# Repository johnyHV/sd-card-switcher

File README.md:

# SD Card Switcher

A simple hardware device for switching a microSD card between a PC and another SD-card host device. 

<div align="center">

</div>

## Use Cases

Useful for devices where an SD card needs to be frequently accessed from both the target device and a PC, for example:

- Firmware development and testing
- Embedded Linux development
- 3D printers
- Single-board computers
- SD-card based embedded devices
- Easy access to logs and configuration files

The switch changes the physical connection of the SD card; it does not copy or synchronize data.

## How it works

The device contains:

* USB interface for connecting the card to a PC
* microSD card slot
* SD-card-shaped PCB with an SD edge connector
* Hardware switch for selecting the active connection

Insert a microSD card into the onboard slot and plug the SD-shaped PCB into the target device.

The switch selects whether the microSD card is connected to:

* **PC** via USB
* **Target device** via the SD card interface

This allows the same SD card to be easily switched between a computer and the target device without physically removing the card.

## Main Components

| Component              | Part                     |
| ---------------------- | ------------------------ |
| USB/SD card controller | GL827                    |
| Bus switch             | SN74CBT3257D             |
| SD card socket         | 693072010801             |
| USB-C connector        | Molex 105450-0101        |
| Micro USB connector    | Molex 54819-0519         |
| Switch                 | SPDT switch              |
| LED                    | LED                      |
| Passives               | Resistors and capacitors |

## Schematic

## PCB

**PCB thickness: 0.8 mm**

The SD-shaped PCB edge connector requires a 0.8 mm PCB thickness to fit properly into a standard SD card slot.

The PCB was manufactured by [JLCPCB](https://jlcpcb.com/?from=GRVYI). This is a referral link. 

## Files

This repository contains the PCB design files and manufacturing files required to build the SD Card Switcher.

## Disclaimer

This project is provided "as is", without any warranty.

The author is not responsible for any damage to SD cards, connected devices, computers, or other hardware resulting from the use, modification, or construction of this project.

Build and use it at your own risk.

## License

Open-source hardware project.

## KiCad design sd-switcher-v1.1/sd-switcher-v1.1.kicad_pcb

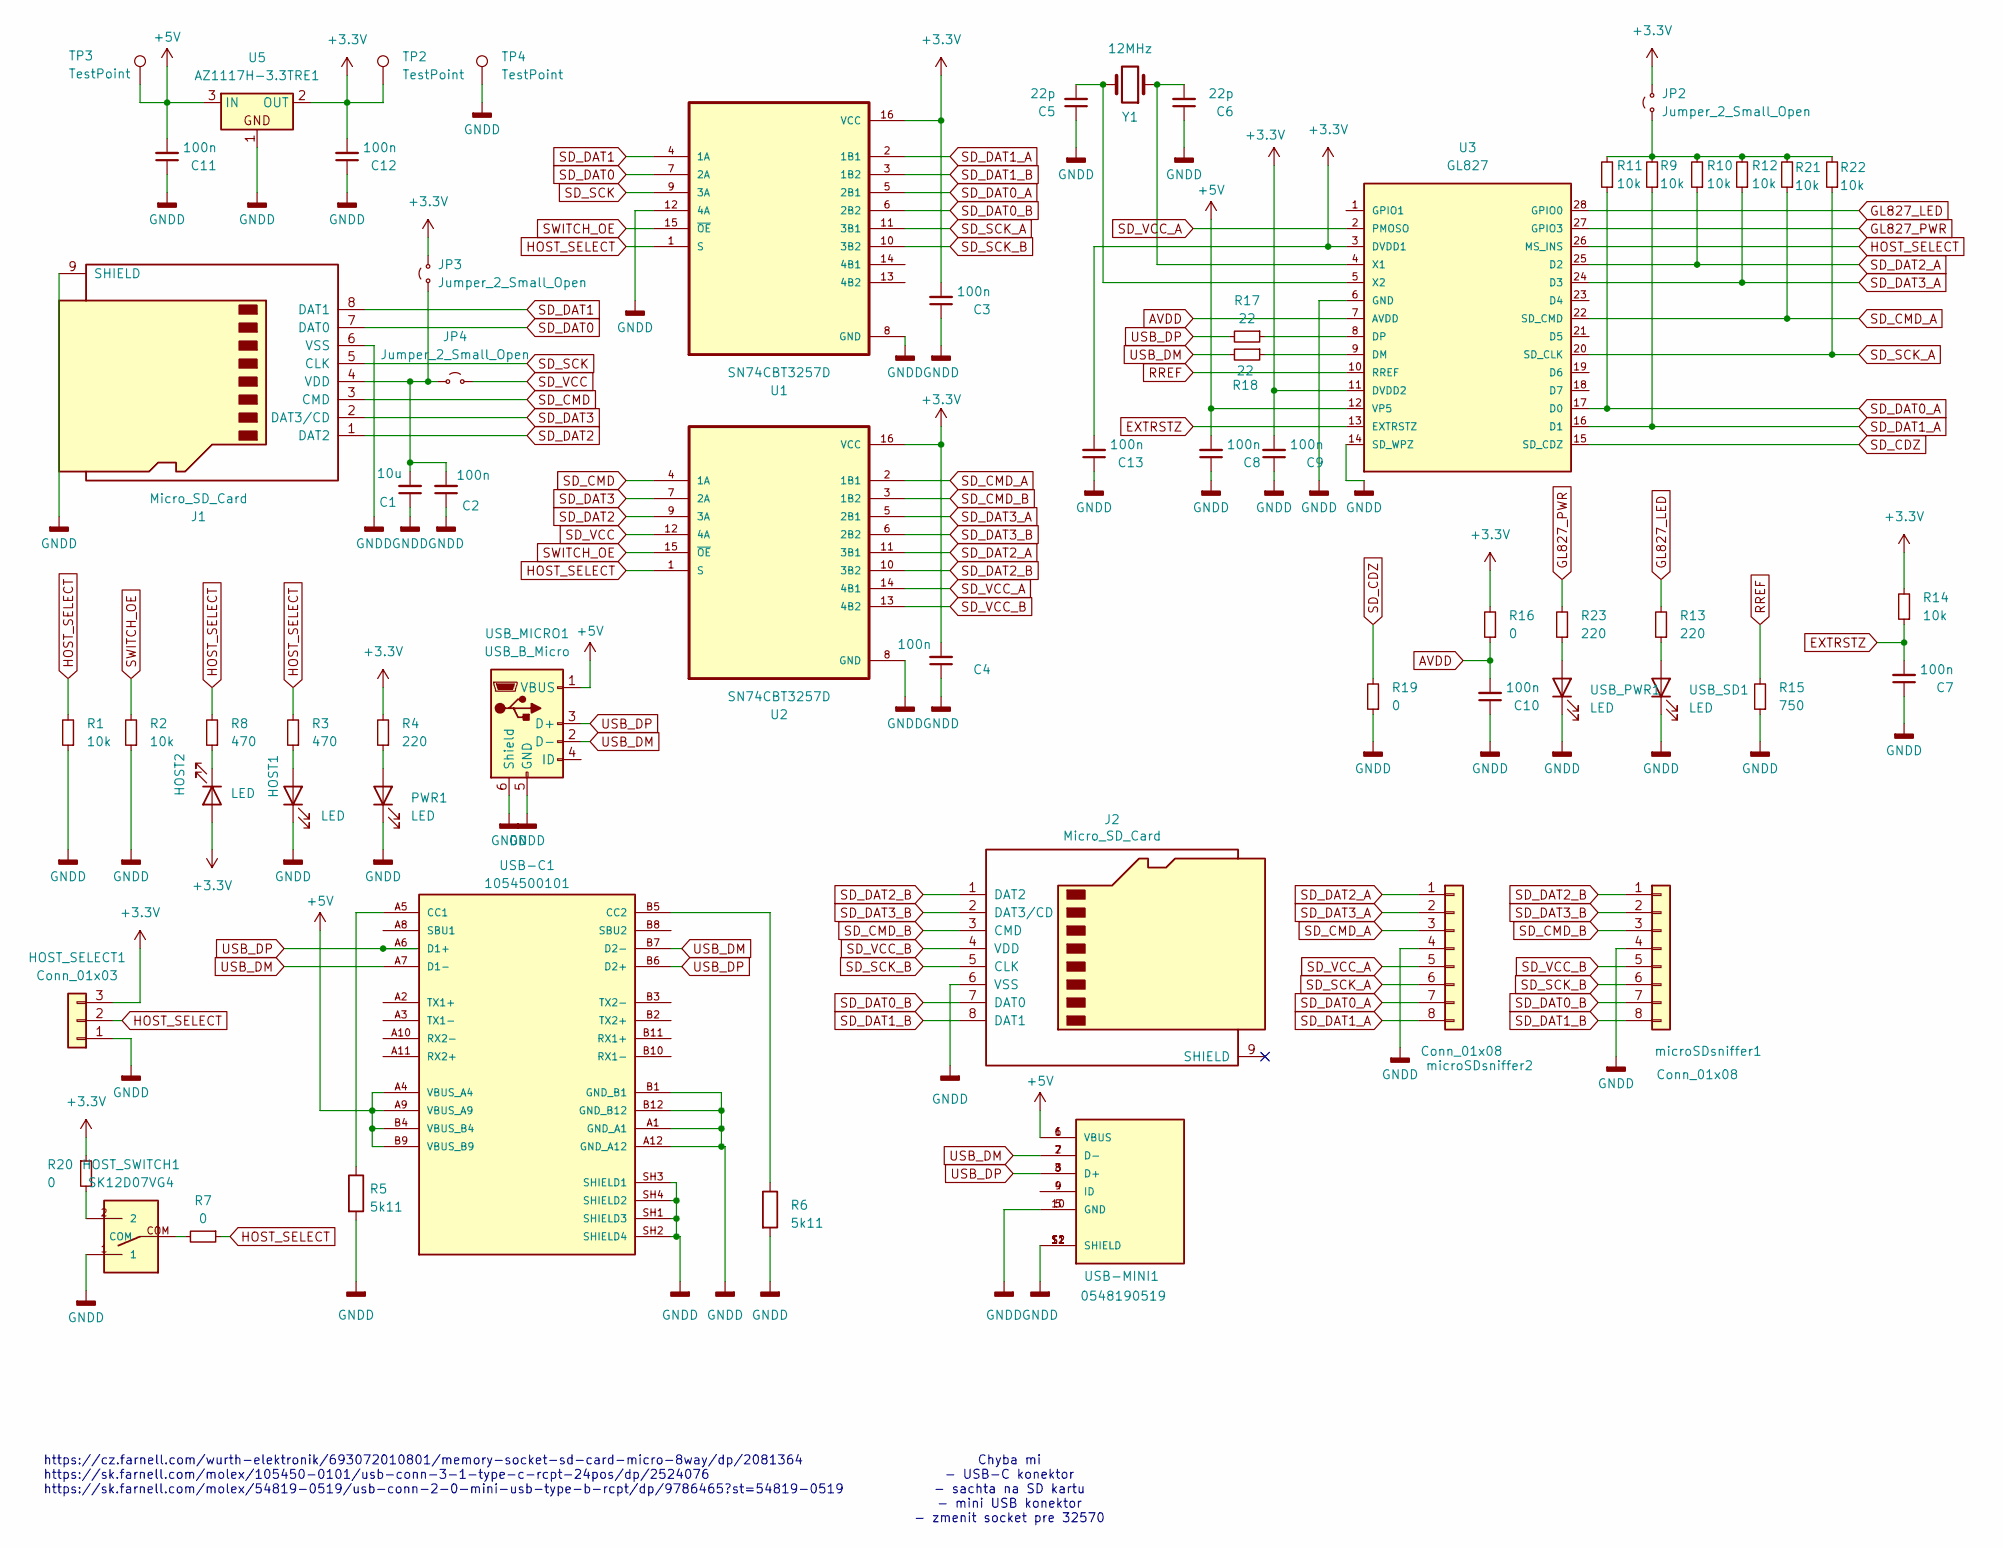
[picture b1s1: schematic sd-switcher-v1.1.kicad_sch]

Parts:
C1: 10u; C_0603_1608Metric
C2, C3, C4, C7, C8, C9, C10, C11, C12, C13: 100n; C_0603_1608Metric
C5, C6: 22p; C_0603_1608Metric
HOST1, HOST2: LED; LED_0805_2012Metric
HOST_SELECT1: Conn_01x03; PinHeader_1x03_P2.54mm_Vertical; Part Number 1-0301FBV0T
HOST_SWITCH1: SK12D07VG4
J1: Micro_SD_Card; microSD_HC_Wuerth_693072010801
J2: Micro_SD_Card; microSD_card
JP2, JP3, JP4: Jumper_2_Small_Open; JUMPER_SMD_1x2
PWR1: LED; LED_0805_2012Metric
R1, R2, R9, R10, R11, R12, R14, R21, R22: 10k; R_0603_1608Metric
R3, R8: 470; R_0603_1608Metric
R4, R13, R23: 220; R_0603_1608Metric
R5, R6: 5k11; R_0603_1608Metric
R7, R16, R19, R20: 0; R_0603_1608Metric
R15: 750; R_0603_1608Metric
R17, R18: 22; R_0603_1608Metric
TP2, TP3, TP4: TestPoint; TestPoint_Pad_D1.0mm
U1, U2: SN74CBT3257D; SOP65P640X110-16N
U3: GL827; SSOP28
U5: AZ1117H-3.3TRE1; SOT-223-3_TabPin2
USB-C1: 1054500101; MOLEX_1054500101; PARTREV A7
USB-MINI1: 0548190519; MOLEX_0548190519; PARTREV A
USB_MICRO1: USB_B_Micro; USB_Micro-B_Amphenol_10104110_Horizontal
USB_PWR1: LED; LED_0805_2012Metric
USB_SD1: LED; LED_0805_2012Metric
Y1: 12MHz; Crystal_SMD_HC49-SD
microSDsniffer1, microSDsniffer2: Conn_01x08; sparkfun sd sniffer

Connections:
+3.3V: C3.2, C4.2, C9.2, C12.2, C13.2, HOST2.2 (A), HOST_SELECT1.3, JP2.2 (B), JP3.2 (B), R4.2, R14.2, R16.2, R20.1, TP2.1, U1.16 (VCC), U2.16 (VCC), U3.3 (DVDD1), U3.11 (DVDD2), U5.2 (OUT)
+5V: C8.2, C11.2, TP3.1, U3.12 (VP5), U5.3 (IN), USB-C1.A4 (VBUS_A4), USB-C1.A9 (VBUS_A9), USB-C1.B4 (VBUS_B4), USB-C1.B9 (VBUS_B9), USB-MINI1.1 (VBUS), USB-MINI1.6 (VBUS), USB_MICRO1.1 (VBUS)
AVDD: C10.2, R16.1, U3.7 (AVDD)
EXTRSTZ: C7.2, R14.1, U3.13 (EXTRSTZ)
GL827_LED: R13.2, U3.28 (GPIO0)
GL827_PWR: R23.2, U3.27 (GPIO3)
GNDD: C1.1, C2.1, C3.1, C4.1, C5.1, C6.1, C7.1, C8.1, C9.1, C10.1, C11.1, C12.1, C13.1, HOST1.1 (K), HOST_SELECT1.1, HOST_SWITCH1.1, J1.6 (VSS), J1.9 (SHIELD), J2.6 (VSS), PWR1.1 (K), R1.1, R2.1, R5.2, R6.2, R15.1, R19.1, TP4.1, U1.8 (GND), U1.12 (4A), U2.8 (GND), U3.6 (GND), U3.14 (SD_WPZ), U5.1, USB-C1.A1 (GND_A1), USB-C1.A12 (GND_A12), USB-C1.B1 (GND_B1), USB-C1.B12 (GND_B12), USB-C1.SH1 (SHIELD3), USB-C1.SH2 (SHIELD4), USB-C1.SH3 (SHIELD1), USB-C1.SH4 (SHIELD2), USB-MINI1.5 (GND), USB-MINI1.10 (GND), USB-MINI1.11 (SHIELD), USB-MINI1.12 (SHIELD), USB-MINI1.S1 (SHIELD), USB-MINI1.S2 (SHIELD), USB_MICRO1.5 (GND), USB_MICRO1.6 (Shield), USB_PWR1.1 (K), USB_SD1.1 (K), microSDsniffer1.4, microSDsniffer2.4
HOST_SELECT: HOST_SELECT1.2, R1.2, R3.2, R7.1, R8.2, U1.1 (S), U2.1 (S), U3.26 (MS_INS)
unnamed: HOST1.2 (A), R3.1
unnamed: HOST2.1 (K), R8.1
unnamed: HOST_SWITCH1.2, R20.2
unnamed: HOST_SWITCH1.COM, R7.2
unnamed: C1.2, C2.2, J1.4 (VDD), JP3.1 (A), JP4.1 (A)
unnamed: JP2.1 (A), R9.2, R10.2, R11.2, R12.2, R21.2, R22.2
unnamed: PWR1.2 (A), R4.1
unnamed: R18.1, U3.9 (DM)
unnamed: R17.1, U3.8 (DP)
unnamed: C6.2, U3.4 (X1), Y1.1
unnamed: C5.2, U3.5 (X2), Y1.2
unnamed: R5.1, USB-C1.A5 (CC1)
unnamed: R6.1, USB-C1.B5 (CC2)
unnamed: USB-MINI1.4 (ID), USB-MINI1.9 (ID)
unnamed: R23.1, USB_PWR1.2 (A)
unnamed: R13.1, USB_SD1.2 (A)
RREF: R15.2, U3.10 (RREF)
SD_CDZ: R19.2, U3.15 (SD_CDZ)
SD_CMD: J1.3 (CMD), U2.4 (1A)
SD_CMD_A: R21.1, U2.2 (1B1), U3.22 (SD_CMD), microSDsniffer2.3
SD_CMD_B: J2.3 (CMD), U2.3 (1B2), microSDsniffer1.3
SD_DAT0: J1.7 (DAT0), U1.7 (2A)
SD_DAT0_A: R11.1, U1.5 (2B1), U3.17 (D0), microSDsniffer2.7
SD_DAT0_B: J2.7 (DAT0), U1.6 (2B2), microSDsniffer1.7
SD_DAT1: J1.8 (DAT1), U1.4 (1A)
SD_DAT1_A: R9.1, U1.2 (1B1), U3.16 (D1), microSDsniffer2.8
SD_DAT1_B: J2.8 (DAT1), U1.3 (1B2), microSDsniffer1.8
SD_DAT2: J1.1 (DAT2), U2.9 (3A)
SD_DAT2_A: R10.1, U2.11 (3B1), U3.25 (D2), microSDsniffer2.1
SD_DAT2_B: J2.1 (DAT2), U2.10 (3B2), microSDsniffer1.1
SD_DAT3: J1.2 (DAT3/CD), U2.7 (2A)
SD_DAT3_A: R12.1, U2.5 (2B1), U3.24 (D3), microSDsniffer2.2
SD_DAT3_B: J2.2 (DAT3/CD), U2.6 (2B2), microSDsniffer1.2
SD_SCK: J1.5 (CLK), U1.9 (3A)
SD_SCK_A: R22.1, U1.11 (3B1), U3.20 (SD_CLK), microSDsniffer2.6
SD_SCK_B: J2.5 (CLK), U1.10 (3B2), microSDsniffer1.6
SD_VCC: JP4.2 (B), U2.12 (4A)
SD_VCC_A: U2.14 (4B1), U3.2 (PMOSO), microSDsniffer2.5
SD_VCC_B: J2.4 (VDD), U2.13 (4B2), microSDsniffer1.5
SWITCH_OE: R2.2, U1.15 (~OE), U2.15 (~OE)
USB_DM: R18.2, USB-C1.A7 (D1-), USB-C1.B7 (D2-), USB-MINI1.2 (D-), USB-MINI1.7 (D-), USB_MICRO1.2 (D-)
USB_DP: R17.2, USB-C1.A6 (D1+), USB-C1.B6 (D2+), USB-MINI1.3 (D+), USB-MINI1.8 (D+), USB_MICRO1.3 (D+)

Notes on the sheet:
https://cz.farnell.com/wurth-elektronik/693072010801/memory-socket-sd-card-micro-8way/dp/2081364 https://sk.farnell.com/molex/105450-0101/usb-conn-3-1-type-c-rcpt-24pos/dp/2524076 https://sk.farnell.com/molex/54819-0519/usb-conn-2-0-mini-usb-type-b-rcpt/dp/9786465?st=54819-0519
Chyba mi - USB-C konektor - sachta na SD kartu - mini USB konektor - zmenit socket pre 32570

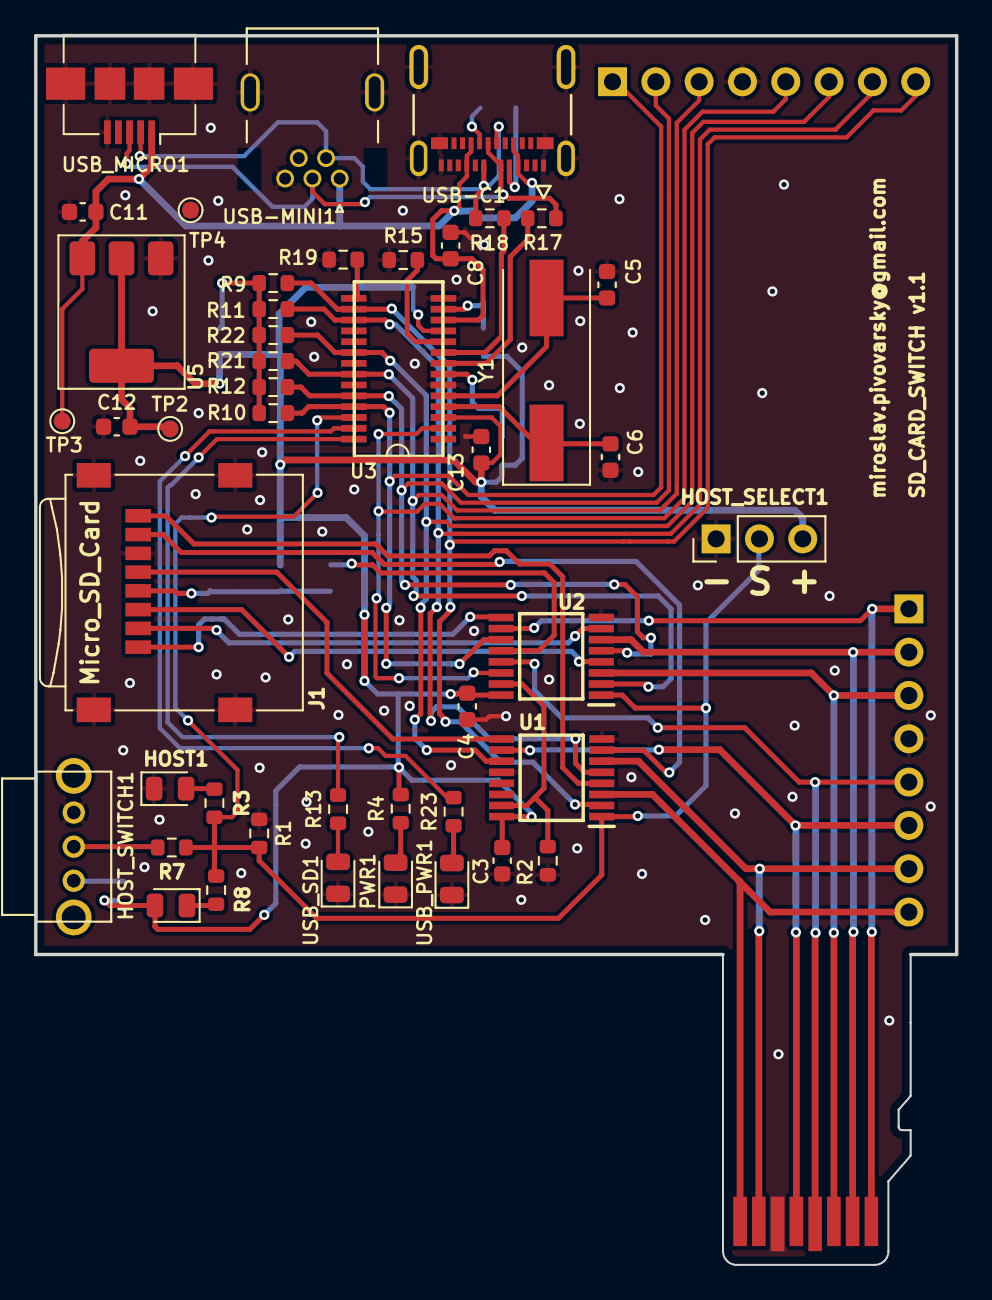
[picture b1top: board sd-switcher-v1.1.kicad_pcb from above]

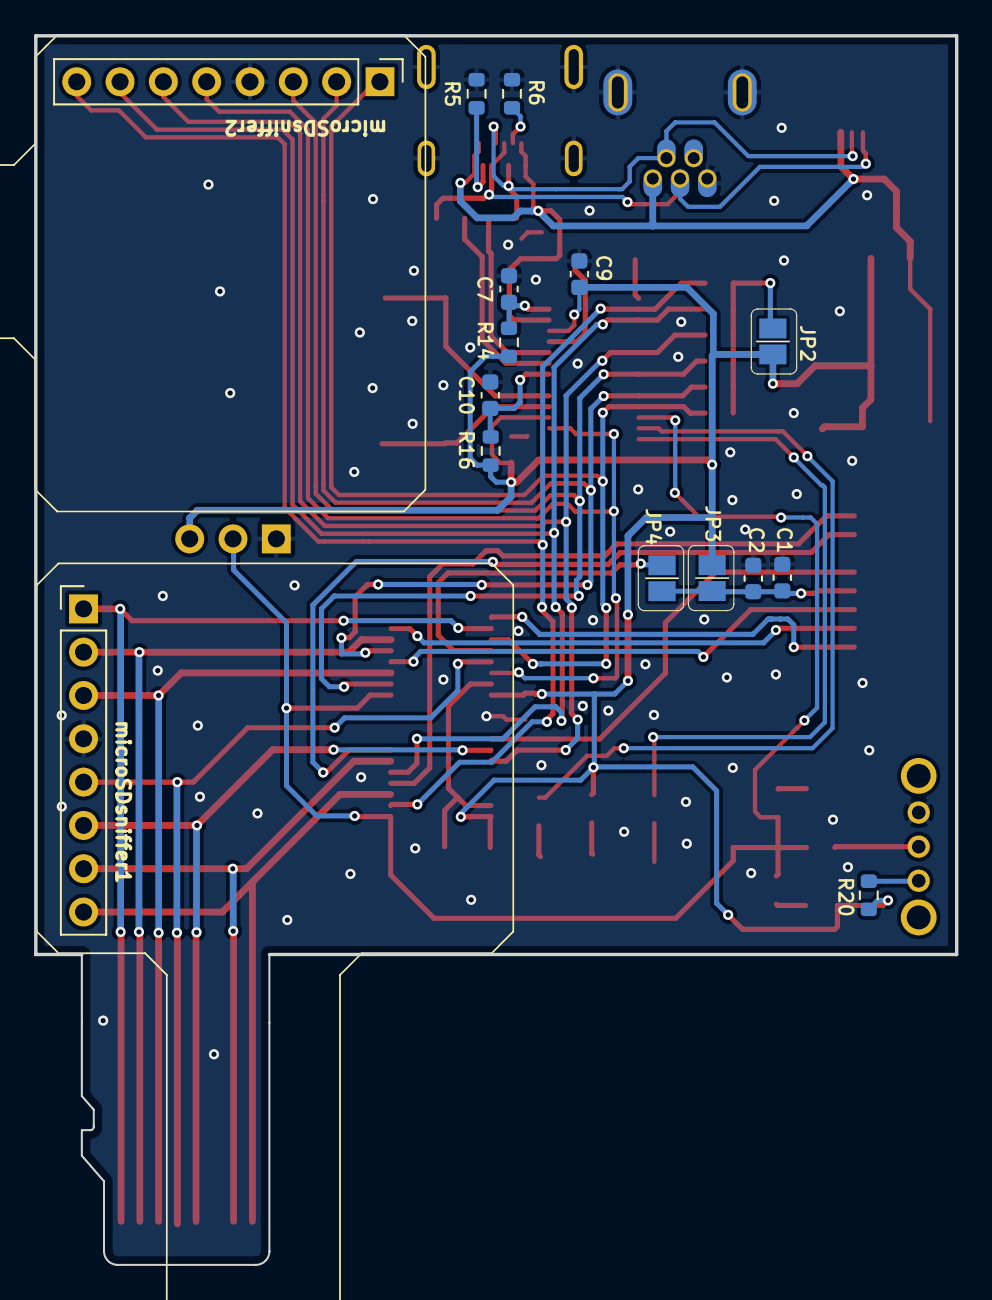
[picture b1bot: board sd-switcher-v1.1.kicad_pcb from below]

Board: 2 copper layers, 54.0 x 72.1 mm, 61 parts (15 on the bottom side), 50 nets.
